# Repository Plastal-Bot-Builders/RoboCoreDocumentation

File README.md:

# RoboCore

RoboCore is a classroom robot kit and coding platform, designed and built in Zambia by **Plastal-Bot Builders** (Lusaka). It has four parts:
- an **ESP32-S3 controller board**;
- a **3D-printed robot** with a parallel lift and a geared gripper;
- a **retail box** with a quick-start guide;
- the **RoboCore IDE**, where students code the robot with blocks or C++.

This repository holds the design sources for all of it: the PCBs, the mechanical design, the software design and the brand. Pitch decks, grant applications and community posts live elsewhere.

<table>
  <tr>
    <td width="50%"></td>
    <td width="50%"></td>
  </tr>
  <tr>
    <td align="center"><b>The robot</b> (V2, Fusion 360)</td>
    <td align="center"><b>The controller board</b> (V2, KiCad 9)</td>
  </tr>
</table>

---

## The controller board (V2)

An XRP-style robot controller on a 68 × 60 mm, 4-layer board. Everything a classroom robot needs is on one board, and it charges and programs over one USB-C cable.

| | |
|---|---|
| **Brain** | ESP32-S3-WROOM-1-N8R2: dual core, Wi-Fi and Bluetooth LE, 8 MB flash, 2 MB PSRAM. Programs over native USB, so no separate programmer is needed |
| **Motors** | 2 DC motors with encoders (DRV8411A dual H-bridge, limited to 1.0 A per motor). JST SH 6-pin, matching the SparkFun XRP motors |
| **Servos** | 4 servo ports on a 5.5 V supply (TPS61089 boost, about 2.5–3 A continuous) |
| **Sensors** | Ultrasonic port (4-pin), 3-channel line-sensor port (5-pin, analog), Qwiic I2C, and an LSM6DSOX 6-axis motion sensor on board |
| **Power** | One Li-ion cell, or several in parallel (3.0–4.2 V), on an XT30 plug. Protected against a reversed or over-voltage pack. USB-C charging at 1 A (MCP73871) and a steady 3.3 V from a buck-boost converter |
| **On board** | RGB LED, buzzer, RESET, BOOT and USER buttons, charge and power LEDs, two 14-pin expansion headers |

<table>
  <tr>
    <td width="50%"></td>
    <td width="50%"></td>
  </tr>
  <tr>
    <td align="center">Top: every port labelled on the silkscreen</td>
    <td align="center">Underside: pin names and the "Designed in Zambia" artwork</td>
  </tr>
  <tr>
    <td></td>
    <td></td>
  </tr>
  <tr>
    <td align="center">The ESP32-S3 module, buttons and IMU</td>
    <td align="center">The connector edge: ultrasonic, battery, USB-C, line sensor, power switch</td>
  </tr>
</table>

- **Design files:** `hardware/controller_v2/`. Open `RoboCore_V2.kicad_pro` in KiCad 9.
- **Renders:** studio renders made in Blender are in `hardware/controller_v2/renders/`, full size and 1600 px, with transparent and white backgrounds. Each shot has a map of where every part sits in the image, for pinouts and highlights in the IDE or on the website. See [its README](hardware/controller_v2/renders/README.md).
- **Before connecting anything:** the sensor headers are not keyed, so a cable can go on backwards. Read [the wrong-plug check](docs/RoboCore_V2_wrong_plug_check.md). Known issues and bring-up findings are kept in [the errata list](docs/RoboCore_V2_errata.md).
- **Sensor boards:** our own 3-channel line sensor and ultrasonic boards are designed in `hardware/sensors/`. For now the robot uses bought-in modules.

## The robot

The current robot (V3, the V-wheel version): an open printed frame with Warren-truss sides, two encoder motors with 56 mm wheels, four V-wheels in wheel wells, a parallel four-bar lift on one MG90S servo (the gripper stays level from the floor to +40 degrees) and a geared gripper on a second servo. The RoboCore V2 controller sits between the side frames, three 18650 cells lie in a printed cradle, the sonar sits in a housing at the front, and a cream rear deck carries an 8 mm Technic/M4 hole grid. 154 x 286 x 111 mm with the lift level, about 620 g; every part prints flat without supports. The V3 model lives in Fusion 360 (document "RoboCore V3 Robot"); the files below are the earlier V2 robot, kept for reference.

- **Model:** `mechanical/robot_v2/RoboCore_V2_Robot.f3d` (Fusion 360) and `.step` (any CAD program).
- **Generator:** the model is built by a Python generator through the Fusion API (`mechanical/robot_v2/fusion/`). [Its README](mechanical/robot_v2/README.md) explains the parameters, the fasteners and the checks: clashes, overhangs, antenna clearance and caster load.
- **Print files:** `mechanical/robot_v2/print/`, already in print orientation. Every part prints without supports on a 180 mm bed.
- **Cardboard version:** a low-cost cardboard chassis template is in `mechanical/robot_v2/cardboard/`.

## The box

<table>
  <tr>
    <td width="50%"></td>
    <td width="50%"></td>
  </tr>
</table>

A printed mailer box, XRP-style, with the quick-start guide printed inside the lid and an insert with a pocket traced from the robot (lift lowered, jaws on the floor) plus a strip for the cable, screws and card. Outer 303 x 213 x 91 mm. The print-ready 1:1 PDFs are in `mechanical/robot_v2/packaging/out_v3/` (generator `make_box_v3.py`; the V2 box is in `out/`).

## Software

- **RoboCore IDE design** (`software/ide_design/`): the screens of the RoboCore IDE, built in Figma by a plugin. It covers block coding (Google Blockly) and C++ (Monaco), a hardware-first block catalogue, and a behaviour spec. The app itself is developed in its own repository, [robocore-ide](https://github.com/Plastal-Bot-Builders/robocore-ide).
- **System architecture** (`software/architecture/`): UML and C4 diagrams of the whole platform, also generated into Figma.
- **Firmware** (`software/firmware/motion/`): an arm-aware braking limiter in C, with tests.

## Brand

<table>
  <tr>
    <td width="33%"></td>
    <td width="33%"></td>
    <td width="33%"></td>
  </tr>
</table>

Event branding is in `design/event_branding/`: roll-up, pop-up, banner, A5 flyer, A4 tri-fold and the brand kit, built in Figma by a plugin. The topographic backgrounds are drawn from Copperbelt elevation data.

---

## Repository layout

```
hardware/          PCB design (KiCad 9)
  controller_v2/     RoboCore V2 controller: project files, libraries (lib/), PCBWay and JLCPCB order
                     packages (fab/), generator, check, costing and Blender render scripts (tools/),
                     silkscreen artwork sources (technicalreference/), studio renders (renders/)
  sensors/           Line sensor (3-channel) and ultrasonic carrier boards for V2
  controller_v1/     RoboCore V1 (ESP32-C3) controller with its fab package and review scripts
  libraries/         Shared symbol and footprint libraries used by V1
  datasheets/        Component datasheets
mechanical/        Mechanical design
  robot_v2/          The Fusion 360 robot: model, Python generator (fusion/), print files (print/),
                     component STEP exports (export/), mailer box (packaging/), cardboard version
                     (cardboard/), vendor models (vendor/), renders
  board_step/        STEP models of the boards, for mechanical integration
  reference/         Motor and XRP reference pictures and models
  chassis_v1_spec/   Specification and script of the V1 chassis
software/          Software
  ide_design/        RoboCore IDE screens (Figma plugin), app icon, block catalogue, behaviour spec
  architecture/      UML + C4 system architecture (Figma plugin)
  firmware/motion/   Arm-aware braking limiter (C, with tests)
design/            Brand
  event_branding/    Roll-up, banner, flyer, tri-fold and brand kit (Figma plugin), topographic maps
docs/              Specification, costing and sourcing, component lists and supplier quote requests,
                   wrong-plug check and errata, schematic PDFs, part photos, A4 technical-reference
                   posters, progress renders, hand-off notes, PCBWay sponsorship request
tools/             sync_from_sources.sh: copies the working sources into this repo
```

## Opening the designs

- **PCB:** open `hardware/controller_v2/RoboCore_V2.kicad_pro` in KiCad 9. Project libraries resolve through `${KIPRJMOD}/lib`; the V1 project's symbol table points at `../libraries`.
- **Robot:** `mechanical/robot_v2/RoboCore_V2_Robot.f3d` opens in Fusion 360; the STEP beside it opens anywhere.
- **Box:** `mechanical/robot_v2/packaging/README.md`. The print files are 1:1 PDFs.
- **Board renders:** `hardware/controller_v2/tools/blender/render_board.sh` re-renders them in Blender 5.1, from the KiCad model.
- **Figma plugins:** the READMEs in `software/ide_design/`, `software/architecture/` and `design/event_branding/` explain how to load and run each plugin.

## Status (2026-10-23)

- **Controller V2:** two assembled prototypes are paid for at PCBWay (order YU1827457, 14 October) and expected to ship around 11 November. Bring-up findings will go into [the errata list](docs/RoboCore_V2_errata.md).
- **Robot:** rev 6. The model and STEP here are Fusion v33.
- **Sensor boards:** designed, not yet ordered. The robot uses bought-in modules for now.
- **IDE:** in development in [robocore-ide](https://github.com/Plastal-Bot-Builders/robocore-ide).
- **Parts:** the component list and supplier quote request for two robots are in `docs/`.

## Keeping this repo up to date

The design work happens in working folders outside this repo. Copy it in, then commit:

```bash
tools/sync_from_sources.sh           # list what changed
tools/sync_from_sources.sh --apply   # copy it in
```

The script lists every source folder it copies. On a slow connection, push large changes in several small commits.

## Licence

MIT, see `LICENSE`. Vendor models under `mechanical/robot_v2/vendor/` keep their own licences, noted in each folder's `SOURCE.txt`.

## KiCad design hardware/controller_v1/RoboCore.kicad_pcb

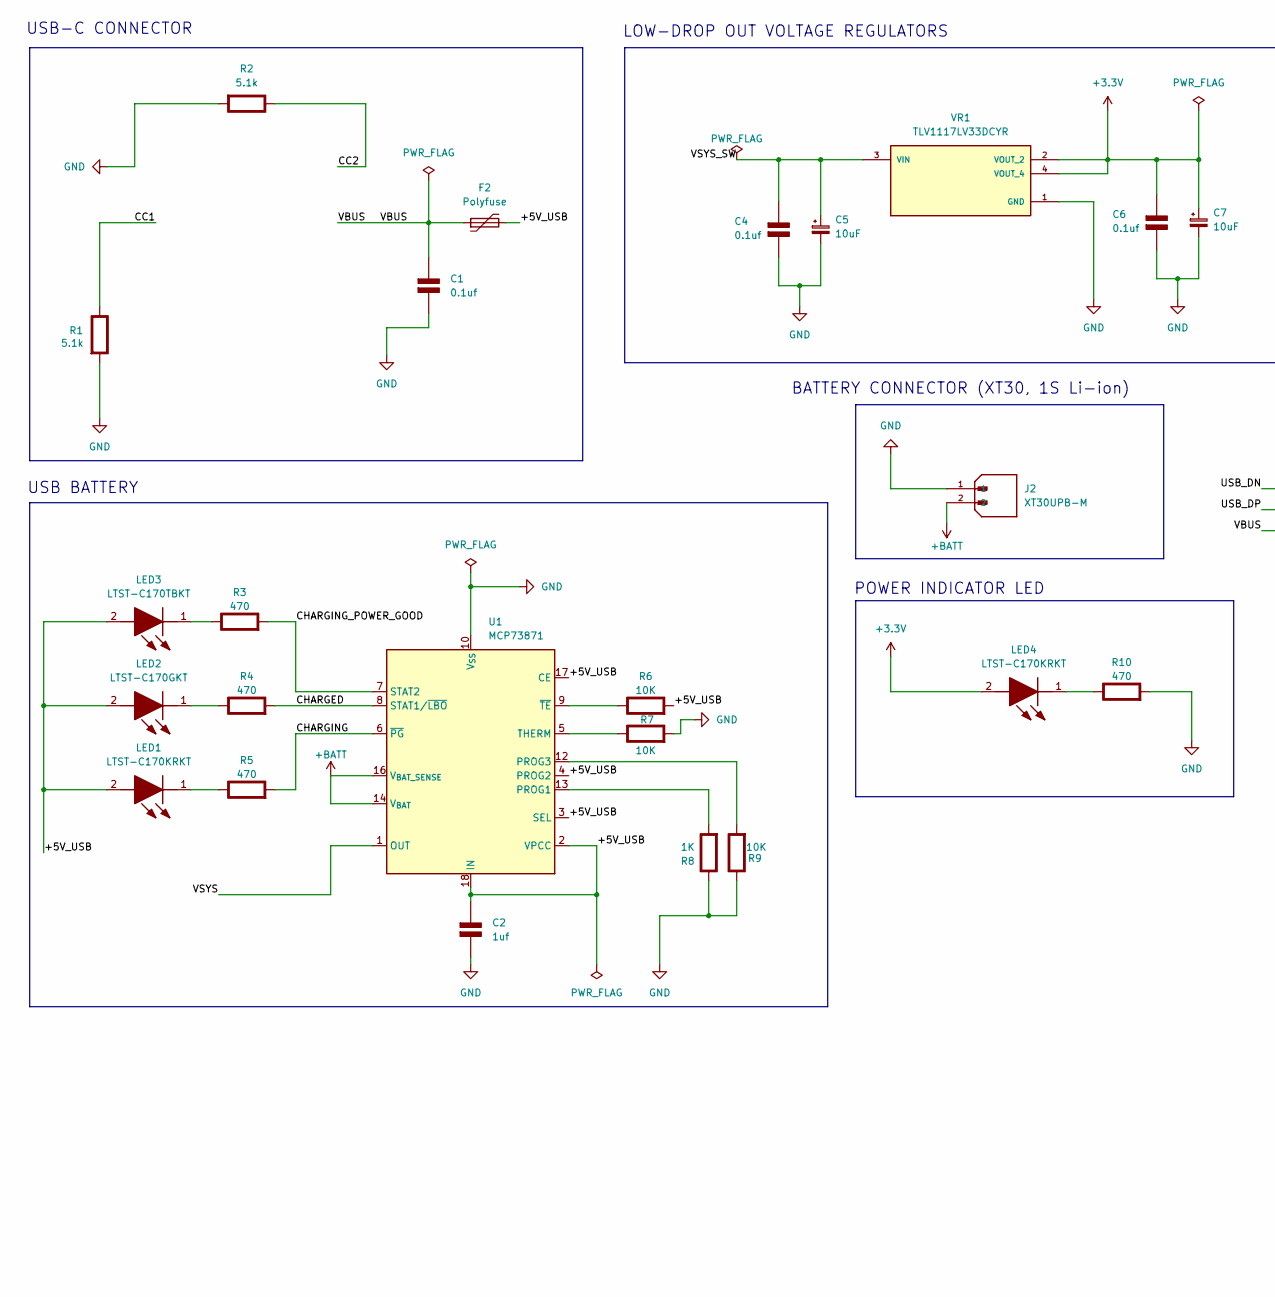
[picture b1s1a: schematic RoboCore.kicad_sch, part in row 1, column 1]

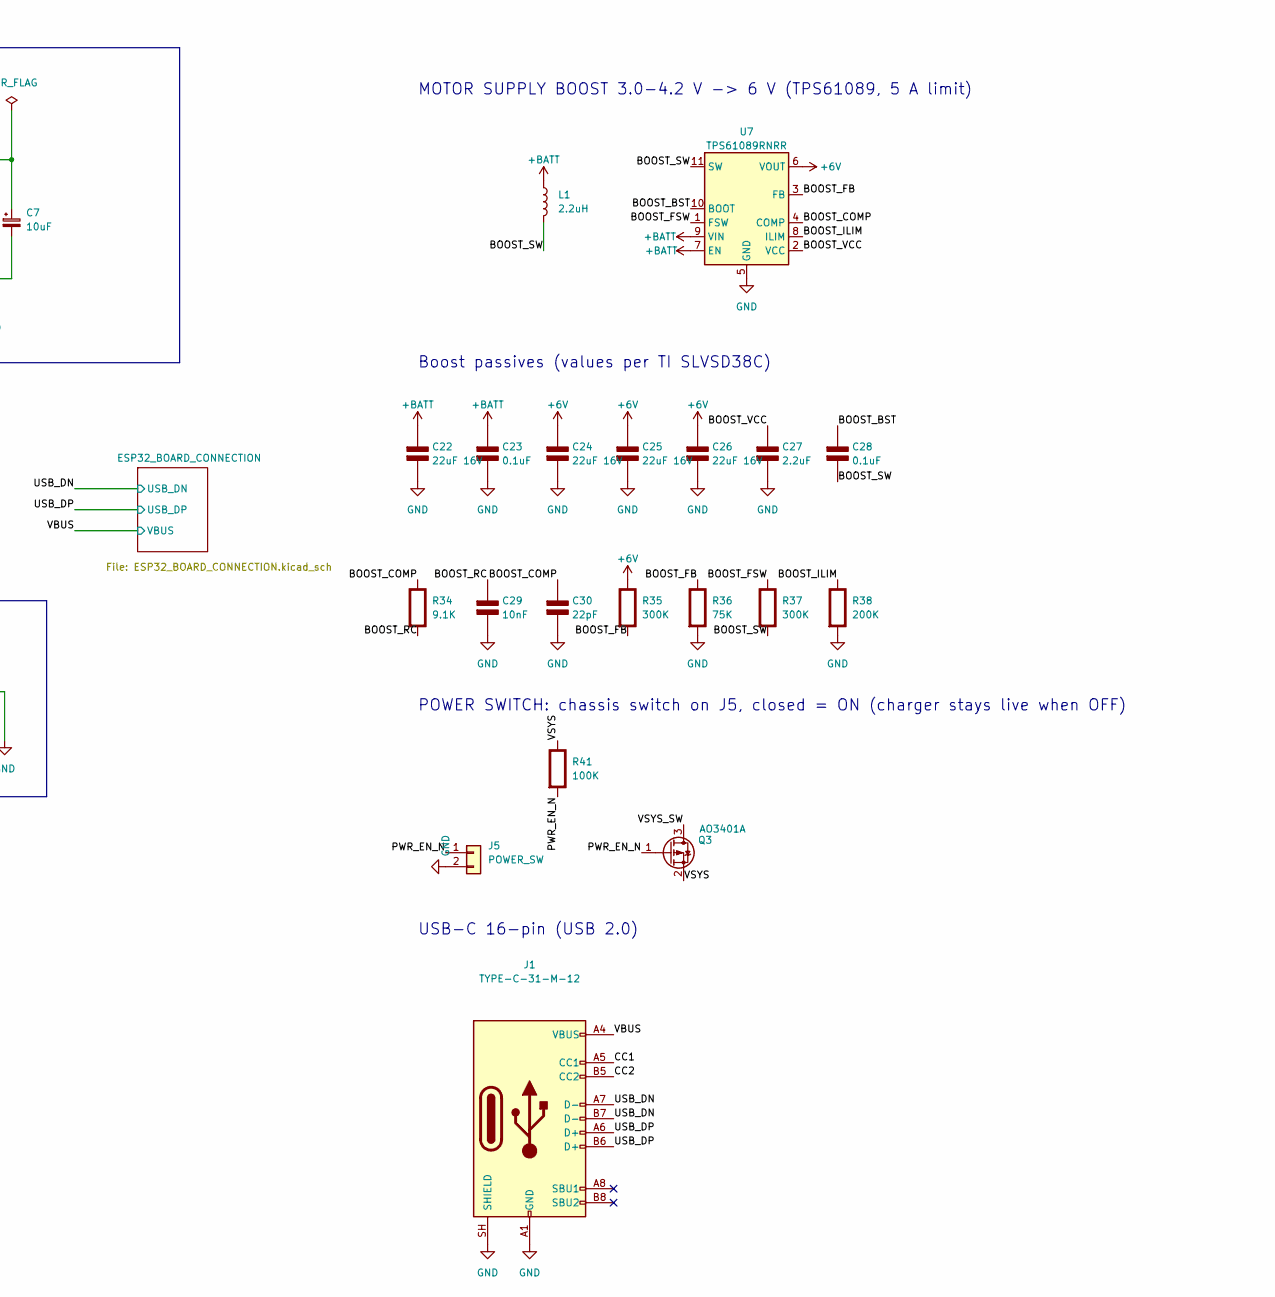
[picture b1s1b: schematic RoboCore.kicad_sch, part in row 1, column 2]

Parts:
C1, C4, C6: 0.1uf; C_0805_2012Metric; Rating V
C2: 1uf; C_0805_2012Metric; Rating V
C5, C7: 10uF; T491A
C22, C24, C25, C26: 22uF 16V; C_1206_3216Metric
C23, C28: 0.1uF; C_0603_1608Metric
C27: 2.2uF; C_0603_1608Metric
C29: 10nF; C_0603_1608Metric
C30: 22pF; C_0603_1608Metric
F2: Polyfuse; FUSSC324X455X250-2N
J1: TYPE-C-31-M-12; USB_C_Receptacle_HRO_TYPE-C-31-M-12
J2: XT30UPB-M; AMASS_XT30UPB-M_1x02_P5.0mm_Vertical; PARTREV N/A
J5: POWER_SW; JST_PH_B2B-PH-K_1x02_P2.00mm_Vertical
L1: 2.2uH; L_Coilcraft_XAL5030-XXX
LED1, LED4: LTST-C170KRKT; LEDC2012X120N; Manufacturer_Part_Number LTST-C170KRKT; Mouser Part Number 859-LTST-C170KRKT
LED2: LTST-C170GKT; LEDC2012X120N; Manufacturer_Part_Number LTST-C170GKT; Mouser Part Number 859-LTST-C170GKT
LED3: LTST-C170TBKT; LEDC2012X120N; Manufacturer_Part_Number LTST-C170TBKT; Mouser Part Number 859-LTST-C170TBKT
Q3: AO3401A; SOT-23
R1, R2: 5.1k; R_0805_2012Metric; Rating W
R3, R4, R5, R10: 470; R_0805_2012Metric; Rating W
R6, R7, R9: 10K; R_0805_2012Metric; Rating W
R8: 1K; R_0805_2012Metric; Rating W
R34: 9.1K; R_0603_1608Metric
R35, R37: 300K; R_0603_1608Metric
R36: 75K; R_0603_1608Metric
R38: 200K; R_0603_1608Metric
R41: 100K; R_0805_2012Metric
U1: MCP73871; QFN-20-1EP_4x4mm_P0.5mm_EP2.5x2.5mm
U7: TPS61089RNRR; Texas_VQFN-RNR0011A-11
VR1: TLV1117LV33DCYR; VREG_LM1117MPX-3.3_NOPB

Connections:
+3.3V: C6.1 (+), C7.1, LED4.2 (A), VR1.2 (VOUT_2), VR1.4 (VOUT_4); also elsewhere on the board
+6V: C24.1 (+), C25.1 (+), C26.1 (+), R35.1 (+), U7.6 (VOUT); also elsewhere on the board
+BATT: C22.1 (+), C23.1 (+), J2.2, L1.1, U1.14 (V_{BAT}), U1.15 (V_{BAT}), U1.16 (V_{BAT_SENSE}), U7.7 (EN), U7.9 (VIN); also elsewhere on the board
/+5V_USB: C2.1 (+), F2.2, LED1.2 (A), LED2.2 (A), LED3.2 (A), R6.2 (-), U1.2 (VPCC), U1.3 (SEL), U1.4 (PROG2), U1.17 (CE), U1.18 (IN), U1.19 (IN)
/BOOST_BST: C28.1 (+), U7.10 (BOOT)
/BOOST_COMP: C30.1 (+), R34.1 (+), U7.4 (COMP)
/BOOST_FB: R35.2 (-), R36.1 (+), U7.3 (FB)
/BOOST_FSW: R37.1 (+), U7.1 (FSW)
/BOOST_ILIM: R38.1 (+), U7.8 (ILIM)
/BOOST_RC: C29.1 (+), R34.2 (-)
/BOOST_SW: C28.2 (-), L1.2, R37.2 (-), U7.11 (SW)
/BOOST_VCC: C27.1 (+), U7.2 (VCC)
/CC1: J1.A5 (CC1), R1.1 (+)
/CC2: J1.B5 (CC2), R2.1 (+)
/CHARGED: R4.2 (-), U1.8 (STAT1/~LBO)
/CHARGING: R5.2 (-), U1.6 (~PG)
/CHARGING_POWER_GOOD: R3.2 (-), U1.7 (STAT2)
/PWR_EN_N: J5.1, Q3.1 (G), R41.2 (-)
/USB_DN: J1.A7 (D-), J1.B7 (D-); also elsewhere on the board
/USB_DP: J1.A6 (D+), J1.B6 (D+); also elsewhere on the board
/VBUS: C1.1 (+), F2.1, J1.A4 (VBUS), J1.A9 (VBUS), J1.B4 (VBUS), J1.B9 (VBUS); also elsewhere on the board
/VSYS: Q3.2 (S), R41.1 (+), U1.1 (OUT), U1.20 (OUT)
/VSYS_SW: C4.1 (+), C5.1, Q3.3 (D), VR1.3 (VIN)
unnamed: LED1.1 (K), R5.1 (+)
unnamed: LED2.1 (K), R4.1 (+)
unnamed: LED3.1 (K), R3.1 (+)
unnamed: LED4.1 (K), R10.1 (+)
unnamed: R6.1 (+), U1.9 (~TE)
unnamed: R7.1 (+), U1.5 (THERM)
unnamed: R8.2 (-), U1.13 (PROG1)
unnamed: R9.2 (-), U1.12 (PROG3)

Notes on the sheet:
USB BATTERY
Boost passives (values per TI SLVSD38C)
POWER INDICATOR LED
BATTERY CONNECTOR (XT30, 1S Li-ion)
LOW-DROP OUT VOLTAGE REGULATORS
USB-C 16-pin (USB 2.0)
MOTOR SUPPLY BOOST 3.0-4.2 V -> 6 V (TPS61089, 5 A limit)
POWER SWITCH: chassis switch on J5, closed = ON (charger stays live when OFF)
USB-C CONNECTOR

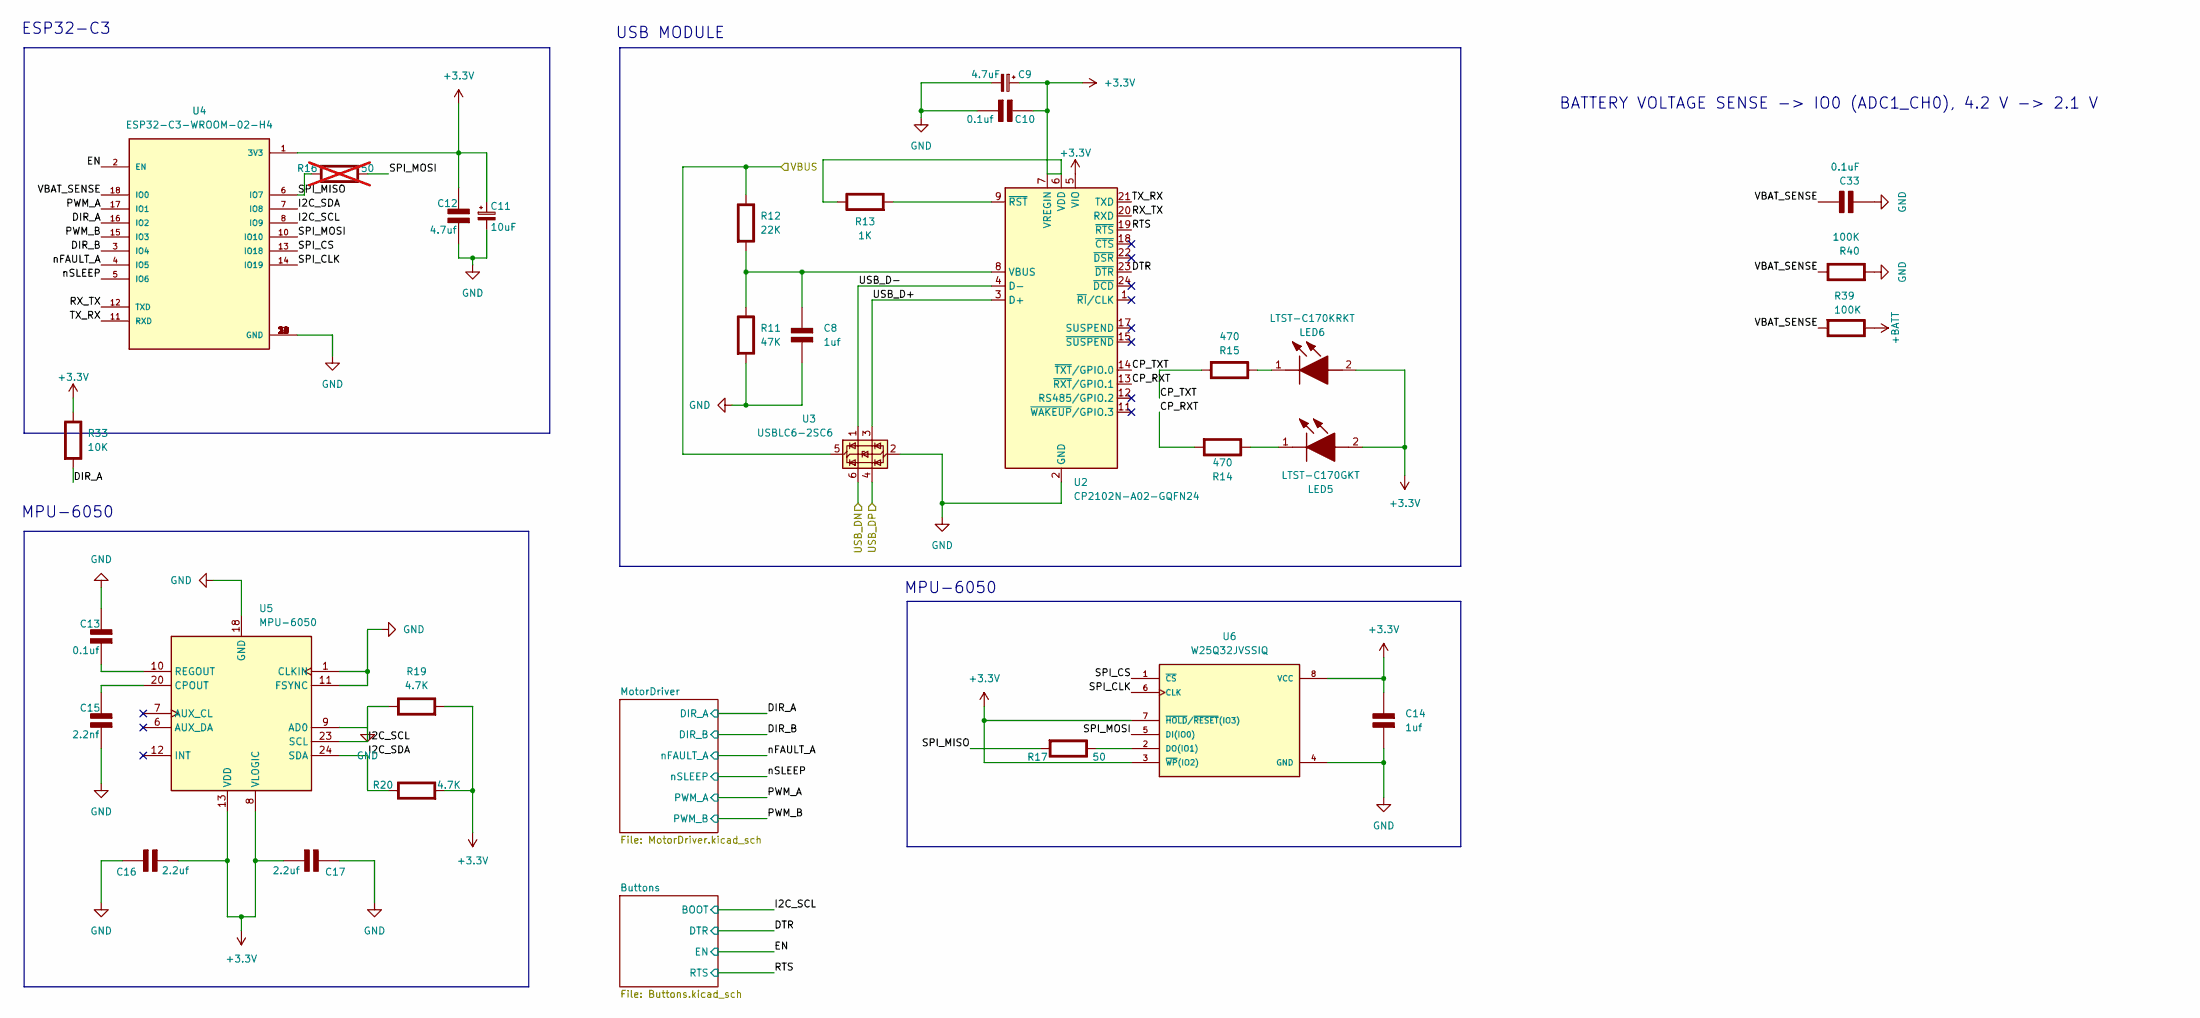
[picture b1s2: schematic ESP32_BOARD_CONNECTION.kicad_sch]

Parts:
C8, C14: 1uf; C_0805_2012Metric; Rating V
C9: 4.7uF; T491A
C10, C13: 0.1uf; C_0805_2012Metric; Rating V
C11: 10uF; T491A
C12: 4.7uf; C_0805_2012Metric; Rating V
C15: 2.2nf; C_0805_2012Metric; Rating V
C16, C17: 2.2uf; C_0805_2012Metric; Rating V
C33: 0.1uF; C_0805_2012Metric
LED5: LTST-C170GKT; LEDC2012X120N; Manufacturer_Part_Number LTST-C170GKT; Mouser Part Number 859-LTST-C170GKT
LED6: LTST-C170KRKT; LEDC2012X120N; Manufacturer_Part_Number LTST-C170KRKT; Mouser Part Number 859-LTST-C170KRKT
R11: 47K; R_0805_2012Metric; Rating W
R12: 22K; R_0805_2012Metric; Rating W
R13: 1K; R_0805_2012Metric; Rating W
R14, R15: 470; R_0805_2012Metric; Rating W
R16: 50; R_0805_2012Metric; Rating W; not fitted
R17: 50; R_0805_2012Metric; Rating W
R19, R20: 4.7K; R_0805_2012Metric; Rating W
R33: 10K; R_0805_2012Metric
R39, R40: 100K; R_0805_2012Metric
U2: CP2102N-A02-GQFN24; QFN-24-1EP_4x4mm_P0.5mm_EP2.6x2.6mm
U3: USBLC6-2SC6; SOT-23-6
U4: ESP32-C3-WROOM-02-H4; MODULE_ESP32-C3-WROOM-02-H4
U5: MPU-6050; InvenSense_QFN-24_4x4mm_P0.5mm
U6: W25Q32JVSSIQ; SOIC127P790X216-8N; M_PART_NUMBER W25QXX

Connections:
+3.3V: C9.1, C10.1 (+), C11.1, C12.2 (-), C14.2 (-), C16.1 (+), C17.1 (+), LED5.2 (A), LED6.2 (A), R13.1 (+), R19.2 (-), R20.2 (-), R33.1 (+), U2.5 (VIO), U2.6 (VDD), U2.7 (VREGIN), U4.1 (3V3), U5.8 (VLOGIC), U5.13 (VDD), U6.3 (~WP(IO2)), U6.7 (~HOLD/~RESET(IO3)), U6.8 (VCC); also elsewhere on the board
+BATT: R39.1 (+); also elsewhere on the board
/ESP32_BOARD_CONNECTION/CP_RXT: R14.2 (-), U2.13 (~RXT/GPIO.1)
/ESP32_BOARD_CONNECTION/CP_TXT: R15.2 (-), U2.14 (~TXT/GPIO.0)
/ESP32_BOARD_CONNECTION/DIR_A: R33.2 (-), U4.16 (IO2); also elsewhere on the board
/ESP32_BOARD_CONNECTION/DIR_B: U4.3 (IO4); also elsewhere on the board
/ESP32_BOARD_CONNECTION/DTR: U2.23 (~DTR); also elsewhere on the board
/ESP32_BOARD_CONNECTION/EN: U4.2 (EN); also elsewhere on the board
/ESP32_BOARD_CONNECTION/I2C_SDA: R20.1 (+), U4.7 (IO8), U5.24 (SDA)
/ESP32_BOARD_CONNECTION/PWM_A: U4.17 (IO1); also elsewhere on the board
/ESP32_BOARD_CONNECTION/PWM_B: U4.15 (IO3); also elsewhere on the board
/ESP32_BOARD_CONNECTION/RTS: U2.19 (~RTS); also elsewhere on the board
/ESP32_BOARD_CONNECTION/RX_TX: U2.20 (RXD), U4.12 (TXD)
/ESP32_BOARD_CONNECTION/SPI_CLK: U4.14 (IO19), U6.6 (CLK)
/ESP32_BOARD_CONNECTION/SPI_CS: U4.13 (IO18), U6.1 (~CS)
/ESP32_BOARD_CONNECTION/SPI_MISO: R16.1 (+), R17.2 (-), U4.6 (IO7)
/ESP32_BOARD_CONNECTION/SPI_MOSI: R16.2 (-), U4.10 (IO10), U6.5 (DI(IO0))
/ESP32_BOARD_CONNECTION/TX_RX: U2.21 (TXD), U4.11 (RXD)
/ESP32_BOARD_CONNECTION/USB_D+: U2.3 (D+), U3.3 (I/O2)
/ESP32_BOARD_CONNECTION/USB_D-: U2.4 (D-), U3.1 (I/O1)
/ESP32_BOARD_CONNECTION/VBAT_SENSE: C33.1 (+), R39.2 (-), R40.1 (+), U4.18 (IO0)
/ESP32_BOARD_CONNECTION/nFAULT_A: U4.4 (IO5); also elsewhere on the board
/ESP32_BOARD_CONNECTION/nSLEEP: U4.5 (IO6); also elsewhere on the board
/USB_DN: U3.6 (I/O1); also elsewhere on the board
/USB_DP: U3.4 (I/O2); also elsewhere on the board
/VBUS: R12.1 (+), U3.5 (VBUS); also elsewhere on the board
unnamed: C8.2 (-), R11.1 (+), R12.2 (-), U2.8 (VBUS)
unnamed: C13.1 (+), U5.10 (REGOUT)
unnamed: C15.2 (-), U5.20 (CPOUT)
unnamed: LED5.1 (K), R14.1 (+)
unnamed: LED6.1 (K), R15.1 (+)
unnamed: R13.2 (-), U2.9 (~RST)
unnamed: R17.1 (+), U6.2 (DO(IO1))

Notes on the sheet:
BATTERY VOLTAGE SENSE -> IO0 (ADC1_CH0), 4.2 V -> 2.1 V
USB MODULE
ESP32-C3
MPU-6050

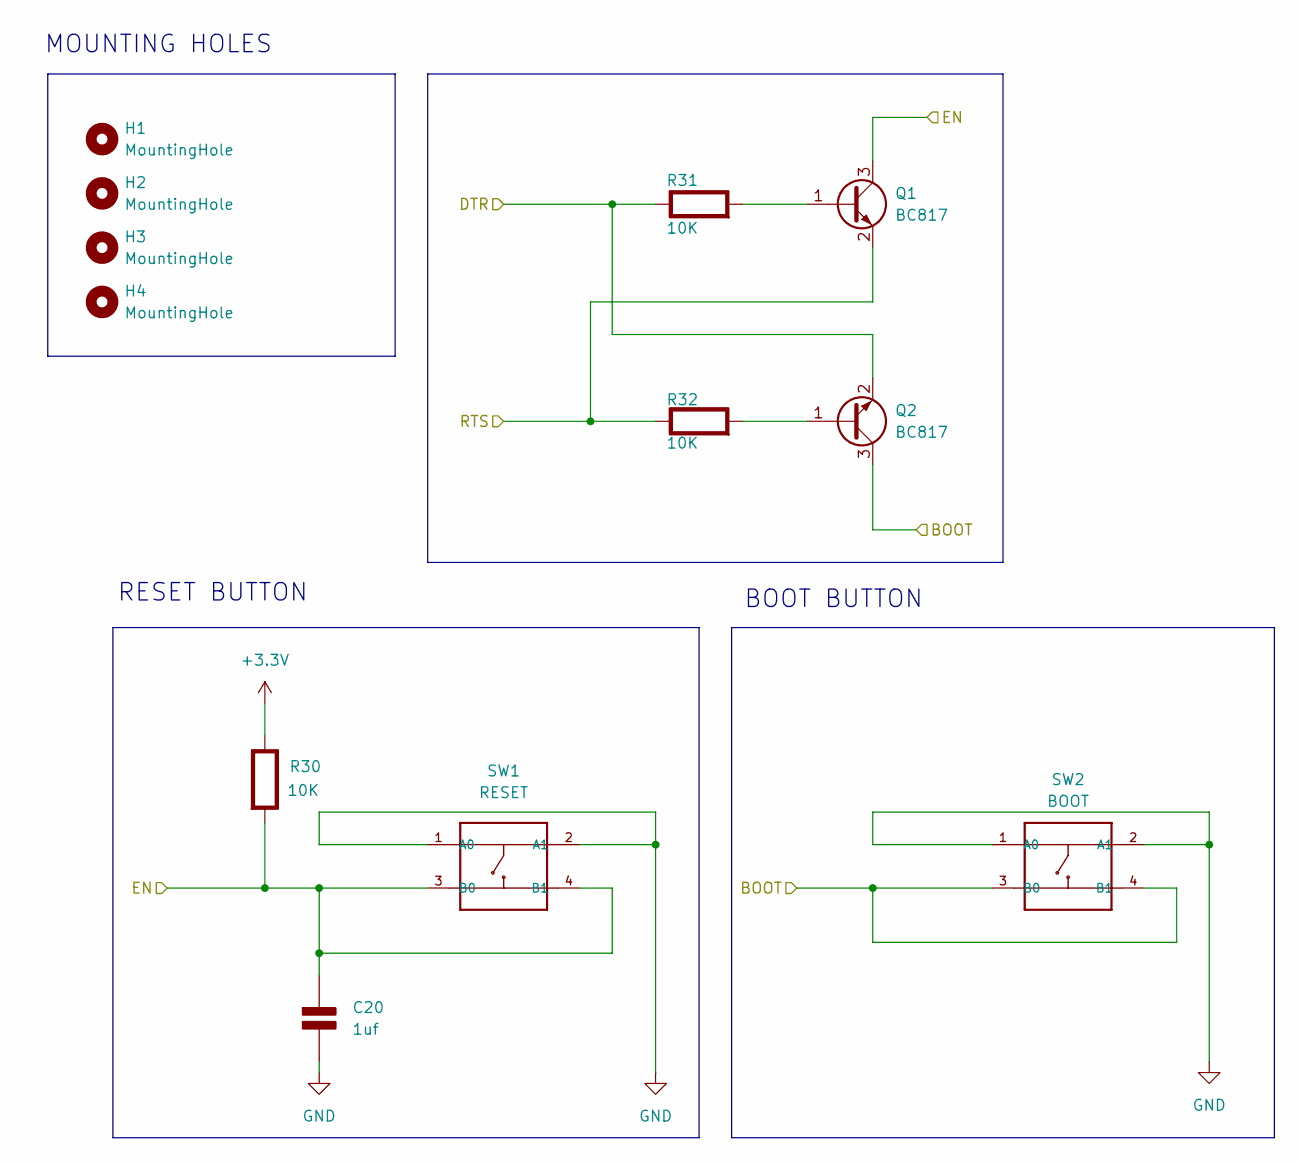
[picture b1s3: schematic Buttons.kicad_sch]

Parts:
C20: 1uf; C_0805_2012Metric; Rating V
H1, H2, H3, H4: MountingHole; MountingHole_2mm
Q1, Q2: BC817; SOT-23
R30, R31, R32: 10K; R_0805_2012Metric; Rating W
SW1: RESET; SW4-SMD-5.2X5.2X1.5MM
SW2: BOOT; SW4-SMD-5.2X5.2X1.5MM

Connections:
+3.3V: R30.1 (+); also elsewhere on the board
/ESP32_BOARD_CONNECTION/DTR: Q2.2 (E), R31.1 (+); also elsewhere on the board
/ESP32_BOARD_CONNECTION/EN: C20.1 (+), Q1.3 (C), R30.2 (-), SW1.3 (B0), SW1.4 (B1); also elsewhere on the board
/ESP32_BOARD_CONNECTION/RTS: Q1.2 (E), R32.1 (+); also elsewhere on the board
unnamed: Q1.1 (B), R31.2 (-)
unnamed: Q2.1 (B), R32.2 (-)

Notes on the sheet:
MOUNTING HOLES
RESET BUTTON
BOOT BUTTON

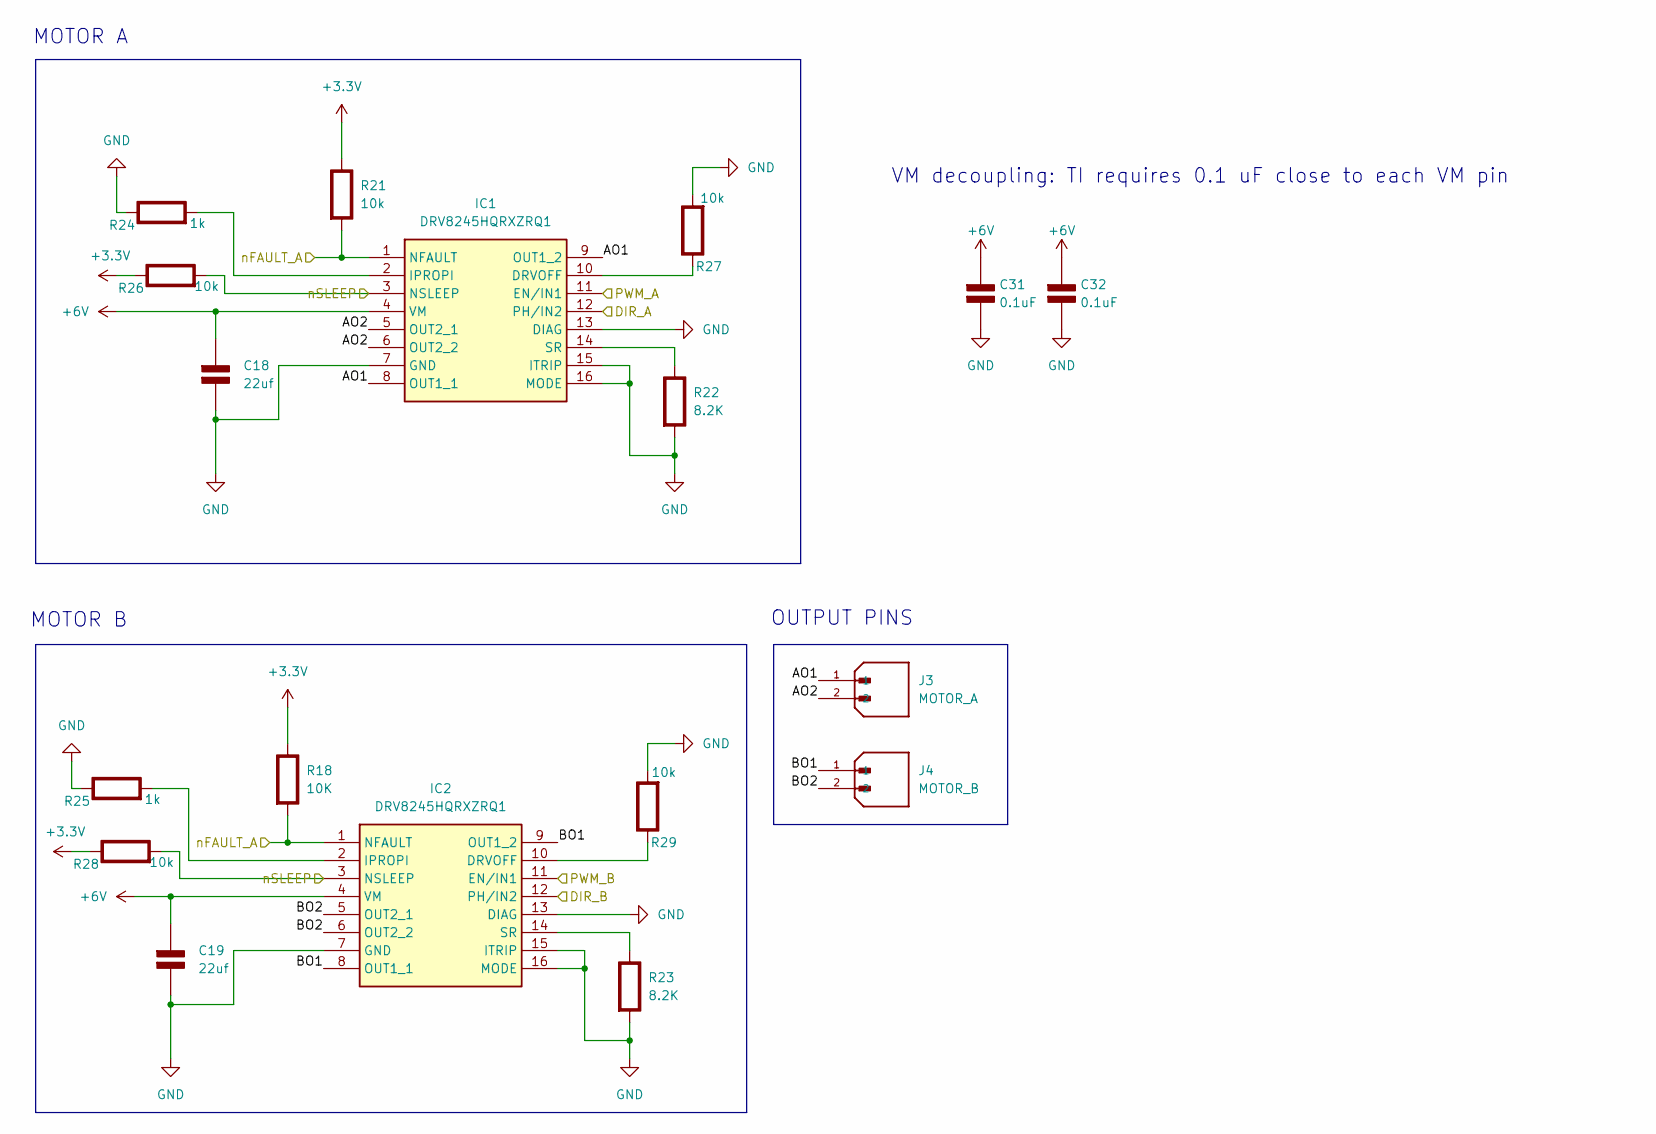
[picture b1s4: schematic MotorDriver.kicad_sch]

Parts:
C18, C19: 22uf; C_0805_2012Metric; Rating V
C31, C32: 0.1uF; C_0805_2012Metric
IC1, IC2: DRV8245HQRXZRQ1; Manufacturer_Part_Number DRV8245HQRXZRQ1; Mouser Part Number 595-DRV8245HQRXZRQ1
J3: MOTOR_A; JST_B2B-PH-SM4-TB; PARTREV N/A
J4: MOTOR_B; JST_B2B-PH-SM4-TB; PARTREV N/A
R18: 10K; R_0805_2012Metric; Rating W
R21, R26, R27, R28, R29: 10k; R_0805_2012Metric; Rating W
R22, R23: 8.2K; R_0805_2012Metric; Rating W
R24, R25: 1k; R_0805_2012Metric; Rating W

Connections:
+3.3V: R18.1 (+), R21.1 (+), R26.1 (+), R28.1 (+); also elsewhere on the board
+6V: C18.1 (+), C19.1 (+), C31.1 (+), C32.1 (+), IC1.4 (VM), IC2.4 (VM); also elsewhere on the board
/ESP32_BOARD_CONNECTION/DIR_A: IC1.12 (PH/IN2); also elsewhere on the board
/ESP32_BOARD_CONNECTION/DIR_B: IC2.12 (PH/IN2); also elsewhere on the board
/ESP32_BOARD_CONNECTION/MotorDriver/AO1: IC1.8 (OUT1_1), IC1.9 (OUT1_2), J3.1
/ESP32_BOARD_CONNECTION/MotorDriver/AO2: IC1.5 (OUT2_1), IC1.6 (OUT2_2), J3.2
/ESP32_BOARD_CONNECTION/MotorDriver/BO1: IC2.8 (OUT1_1), IC2.9 (OUT1_2), J4.1
/ESP32_BOARD_CONNECTION/MotorDriver/BO2: IC2.5 (OUT2_1), IC2.6 (OUT2_2), J4.2
/ESP32_BOARD_CONNECTION/PWM_A: IC1.11 (EN/IN1); also elsewhere on the board
/ESP32_BOARD_CONNECTION/PWM_B: IC2.11 (EN/IN1); also elsewhere on the board
/ESP32_BOARD_CONNECTION/nFAULT_A: IC1.1 (NFAULT), IC2.1 (NFAULT), R18.2 (-), R21.2 (-); also elsewhere on the board
/ESP32_BOARD_CONNECTION/nSLEEP: IC1.3 (NSLEEP), IC2.3 (NSLEEP), R26.2 (-), R28.2 (-); also elsewhere on the board
unnamed: IC1.10 (DRVOFF), R27.1 (+)
unnamed: IC1.2 (IPROPI), R24.2 (-)
unnamed: IC1.14 (SR), R22.1 (+)
unnamed: IC2.10 (DRVOFF), R29.1 (+)
unnamed: IC2.2 (IPROPI), R25.2 (-)
unnamed: IC2.14 (SR), R23.1 (+)

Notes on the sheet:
VM decoupling: TI requires 0.1 uF close to each VM pin
MOTOR A
OUTPUT PINS
MOTOR B

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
